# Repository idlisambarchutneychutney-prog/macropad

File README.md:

## Macropad

A custom 9-key macropad powered by the **Seeed XIAO RP2040** microcontroller running **KMK Firmware** on CircuitPython. Featuring a 3x3 key matrix, an EC11 rotary encoder for media control, a 0.91" OLED status display, and per-key SK6812MINI-E RGB lighting.

---

## Features

- **Brain:** Seeed XIAO RP2040 Microcontroller
- **Key Matrix:** 9 MX switches configured in a 3x3 matrix with 1N4148 diodes (`COL2ROW`).
- **Rotary Encoder:** EC11 encoder mapped to Volume Down, Volume Up, and Mute (push button).
- **Display:** 0.91" I2C OLED display (128x32) running custom status text.
- **Lighting:** 9x SK6812MINI-E addressable per-key RGB LEDs.
- **Firmware:** KMK Firmware (CircuitPython) with built-in productivity macros and application launchers.

---

## Keymap & Macro Layout

| Key Position | Action / Macro | Description |
| :--- | :--- | :--- |
| **Top Left** | `Ctrl + C` | Copy |
| **Top Middle** | `Ctrl + V` | Paste |
| **Top Right** | `Ctrl + Z` | Undo |
| **Mid Left** | Macro | Opens GitHub in browser via Windows Run |
| **Mid Middle** | Macro | Launches VS Code via Windows Run |
| **Mid Right** | Macro | Launches Google Chrome via Windows Run |
| **Bot Left** | Macro | System Shutdown (`shutdown /s /t 0`) |
| **Bot Middle** | Macro | System Restart (`shutdown /r /t 0`) |
| **Bot Right** | `Win + L` | Lock Windows PC |

### Encoder Controls
- **Rotate CCW:** Volume Down (`KC.VOLD`)
- **Rotate CW:** Volume Up (`KC.VOLU`)
- **Press Button:** Mute Audio (`KC.MUTE`)

---

## Hardware & Bill of Materials (BOM)

| Component | Quantity | Description |
| :--- | :--- | :--- |
| Microcontroller | 1 | Seeed Studio XIAO RP2040 |
| Switches | 9 | MX-compatible mechanical switches |
| Diodes | 9 | 1N4148 switching diodes |
| Rotary Encoder | 1 | EC11 Rotary Encoder with push switch |
| Display | 1 | 0.91" I2C OLED Display Module (128x32) |
| RGB LEDs | 9 | SK6812MINI-E surface-mount LEDs |
| Custom PCB | 1 | Designed in KiCad |
| Enclosure | 1 | 3D-printed enclosure designed in Onshape |

---

## Pinout & Schematic Mapping

| Peripheral | Component Pin | XIAO RP2040 Pin |
| :--- | :--- | :--- |
| **Matrix Columns** | Col 0, Col 1, Col 2 | `D5`, `D3`, `D6` |
| **Matrix Rows** | Row 0, Row 1, Row 2 | `D4`, `D1`, `D0` |
| **Encoder** | Pin A, Pin B, Switch | `D8`, `D9`, `D7` |
| **OLED Display** | SCL, SDA | `D2`, `D10` |
| **RGB LED Chain** | Data In (DIN) | `D7` |

---

## Hardware Gallery

### Schematic Diagram

### PCB Design

### 3D Enclosure Render

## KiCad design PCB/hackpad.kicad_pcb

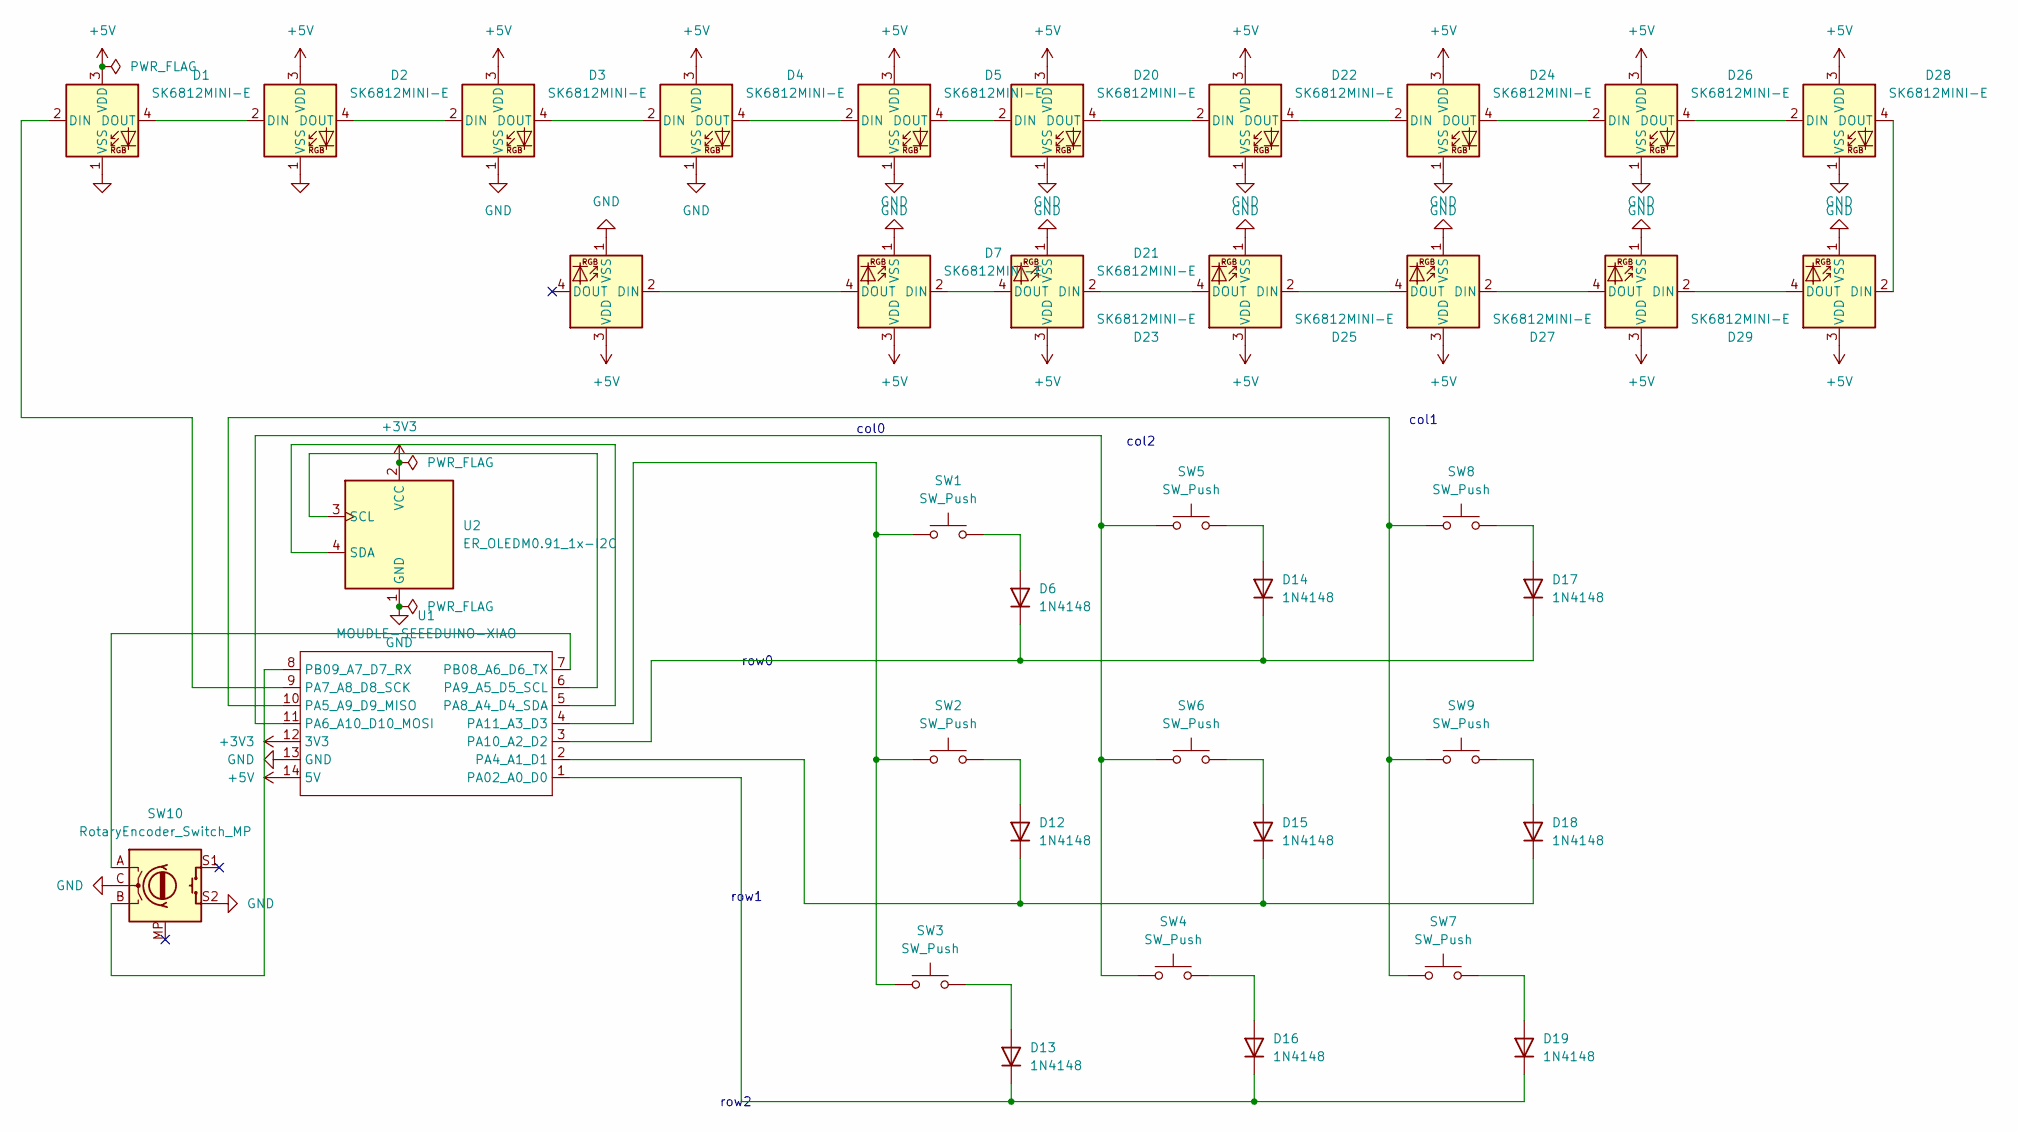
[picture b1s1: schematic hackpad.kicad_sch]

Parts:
D1, D2, D3, D4, D5, D7, D9, D20, D21, D22, D23, D24, D25, D26, D27, D28, D29: SK6812MINI-E; LED_SK6812MINI-E_3.2x2.8mm_P1.5mm_ReverseMount
D6, D12, D13, D14, D15, D16, D17, D18, D19: 1N4148; D_DO-35_SOD27_P7.62mm_Horizontal
SW1, SW2, SW3, SW4, SW5, SW6, SW7, SW8, SW9: SW_Push; SW_Cherry_MX_1.00u_PCB
SW10: RotaryEncoder_Switch_MP; RotaryEncoder_Alps_EC11E-Switch_Vertical_H20mm
U1: MOUDLE-SEEEDUINO-XIAO; XIAO-Generic-Hybrid-14P-2.54-21X17.8MM
U2: ER_OLEDM0.91_1x-I2C

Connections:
+3V3: U1.12 (3V3), U2.2 (VCC)
+5V: D1.3 (VDD), D2.3 (VDD), D3.3 (VDD), D4.3 (VDD), D5.3 (VDD), D7.3 (VDD), D9.3 (VDD), D20.3 (VDD), D21.3 (VDD), D22.3 (VDD), D23.3 (VDD), D24.3 (VDD), D25.3 (VDD), D26.3 (VDD), D27.3 (VDD), D28.3 (VDD), D29.3 (VDD), U1.14 (5V)
GND: D1.1 (VSS), D2.1 (VSS), D3.1 (VSS), D4.1 (VSS), D5.1 (VSS), D7.1 (VSS), D9.1 (VSS), D20.1 (VSS), D21.1 (VSS), D22.1 (VSS), D23.1 (VSS), D24.1 (VSS), D25.1 (VSS), D26.1 (VSS), D27.1 (VSS), D28.1 (VSS), D29.1 (VSS), SW10.C, SW10.S2, U1.13 (GND), U2.1 (GND)
unnamed: D1.2 (DIN), U1.9 (PA7_A8_D8_SCK)
unnamed: D1.4 (DOUT), D2.2 (DIN)
unnamed: D2.4 (DOUT), D3.2 (DIN)
unnamed: D3.4 (DOUT), D4.2 (DIN)
unnamed: D4.4 (DOUT), D5.2 (DIN)
unnamed: D6.2 (A), SW1.2
unnamed: D7.4 (DOUT), D9.2 (DIN)
unnamed: D12.2 (A), SW2.2
unnamed: D12.1 (K), D15.1 (K), D18.1 (K), U1.2 (PA4_A1_D1)
unnamed: D13.2 (A), SW3.2
unnamed: D13.1 (K), D16.1 (K), D19.1 (K), U1.1 (PA02_A0_D0)
unnamed: D14.2 (A), SW5.2
unnamed: D6.1 (K), D14.1 (K), D17.1 (K), U1.3 (PA10_A2_D2)
unnamed: D15.2 (A), SW6.2
unnamed: D16.2 (A), SW4.2
unnamed: D17.2 (A), SW8.2
unnamed: D18.2 (A), SW9.2
unnamed: D19.2 (A), SW7.2
unnamed: D5.4 (DOUT), D20.2 (DIN)
unnamed: D20.4 (DOUT), D22.2 (DIN)
unnamed: D21.2 (DIN), D23.4 (DOUT)
unnamed: D7.2 (DIN), D21.4 (DOUT)
unnamed: D22.4 (DOUT), D24.2 (DIN)
unnamed: D23.2 (DIN), D25.4 (DOUT)
unnamed: D24.4 (DOUT), D26.2 (DIN)
unnamed: D25.2 (DIN), D27.4 (DOUT)
unnamed: D26.4 (DOUT), D28.2 (DIN)
unnamed: D27.2 (DIN), D29.4 (DOUT)
unnamed: D28.4 (DOUT), D29.2 (DIN)
unnamed: SW7.1, SW8.1, SW9.1, U1.10 (PA5_A9_D9_MISO)
unnamed: SW4.1, SW5.1, SW6.1, U1.11 (PA6_A10_D10_MOSI)
unnamed: U1.5 (PA8_A4_D4_SDA), U2.4 (SDA)
unnamed: U1.6 (PA9_A5_D5_SCL), U2.3 (SCL)
unnamed: SW1.1, SW2.1, SW3.1, U1.4 (PA11_A3_D3)
unnamed: SW10.A, U1.7 (PB08_A6_D6_TX)
unnamed: SW10.B, U1.8 (PB09_A7_D7_RX)

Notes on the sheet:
col0
col1
row1
col2
row2
row0

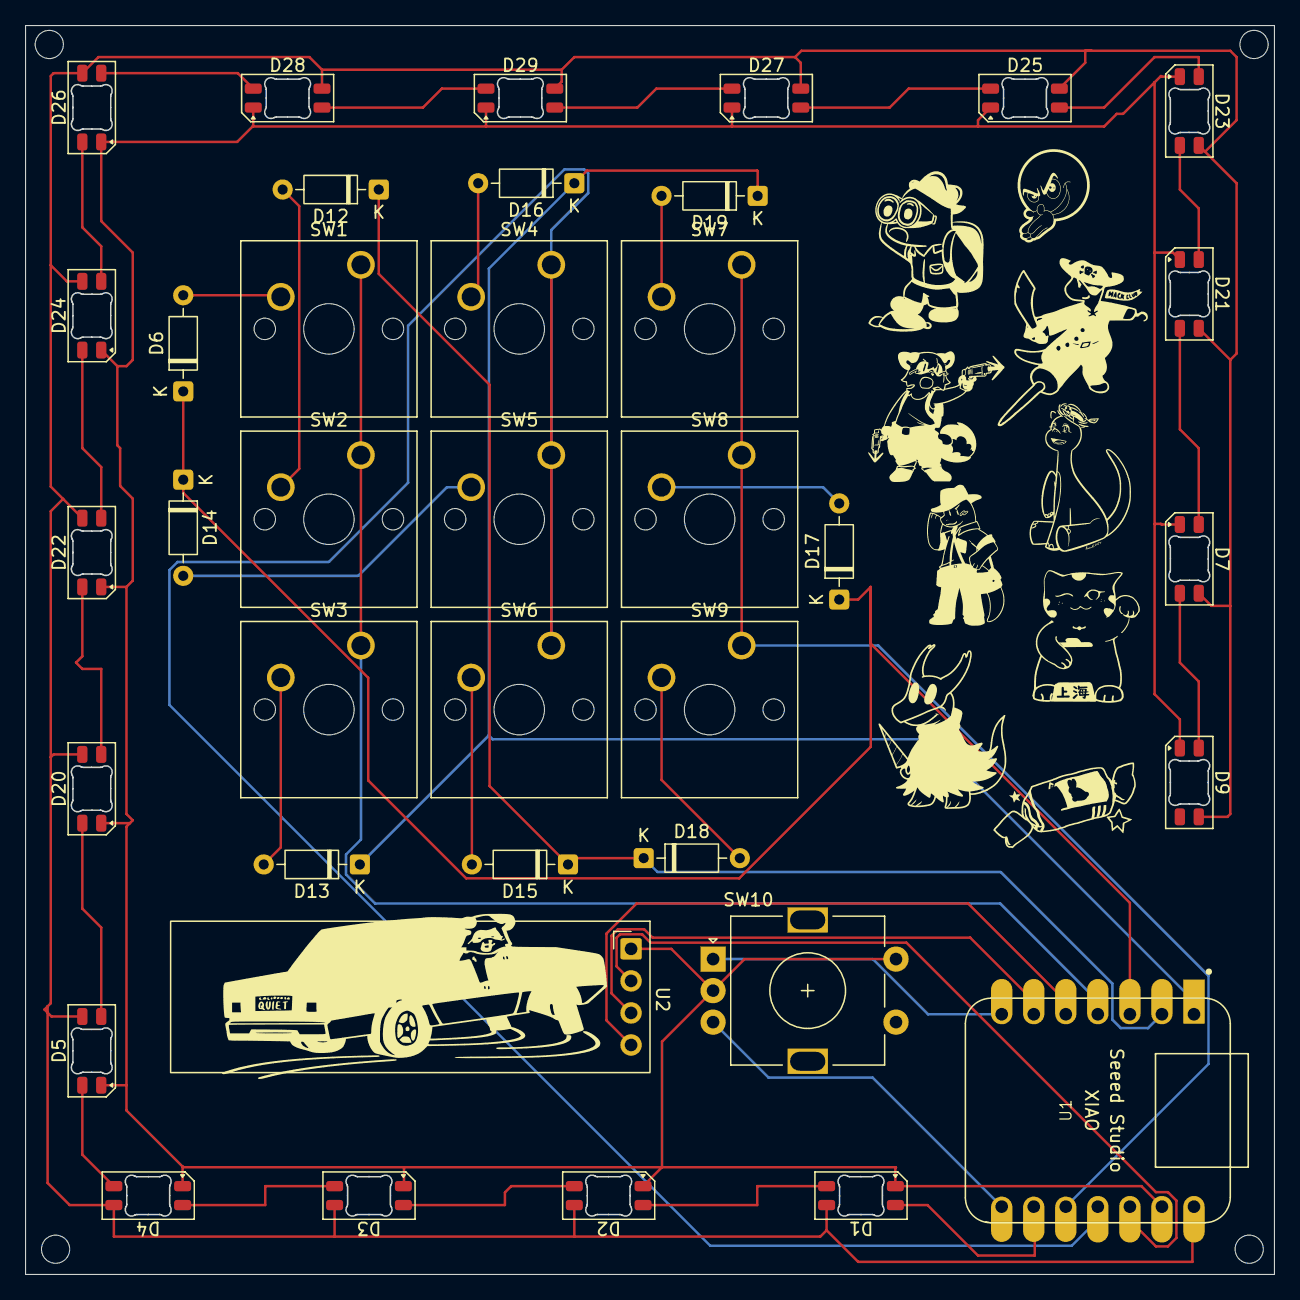
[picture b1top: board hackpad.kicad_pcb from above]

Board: 2 copper layers, 99.0 x 99.0 mm, 38 parts (0 on the bottom side), 39 nets.
